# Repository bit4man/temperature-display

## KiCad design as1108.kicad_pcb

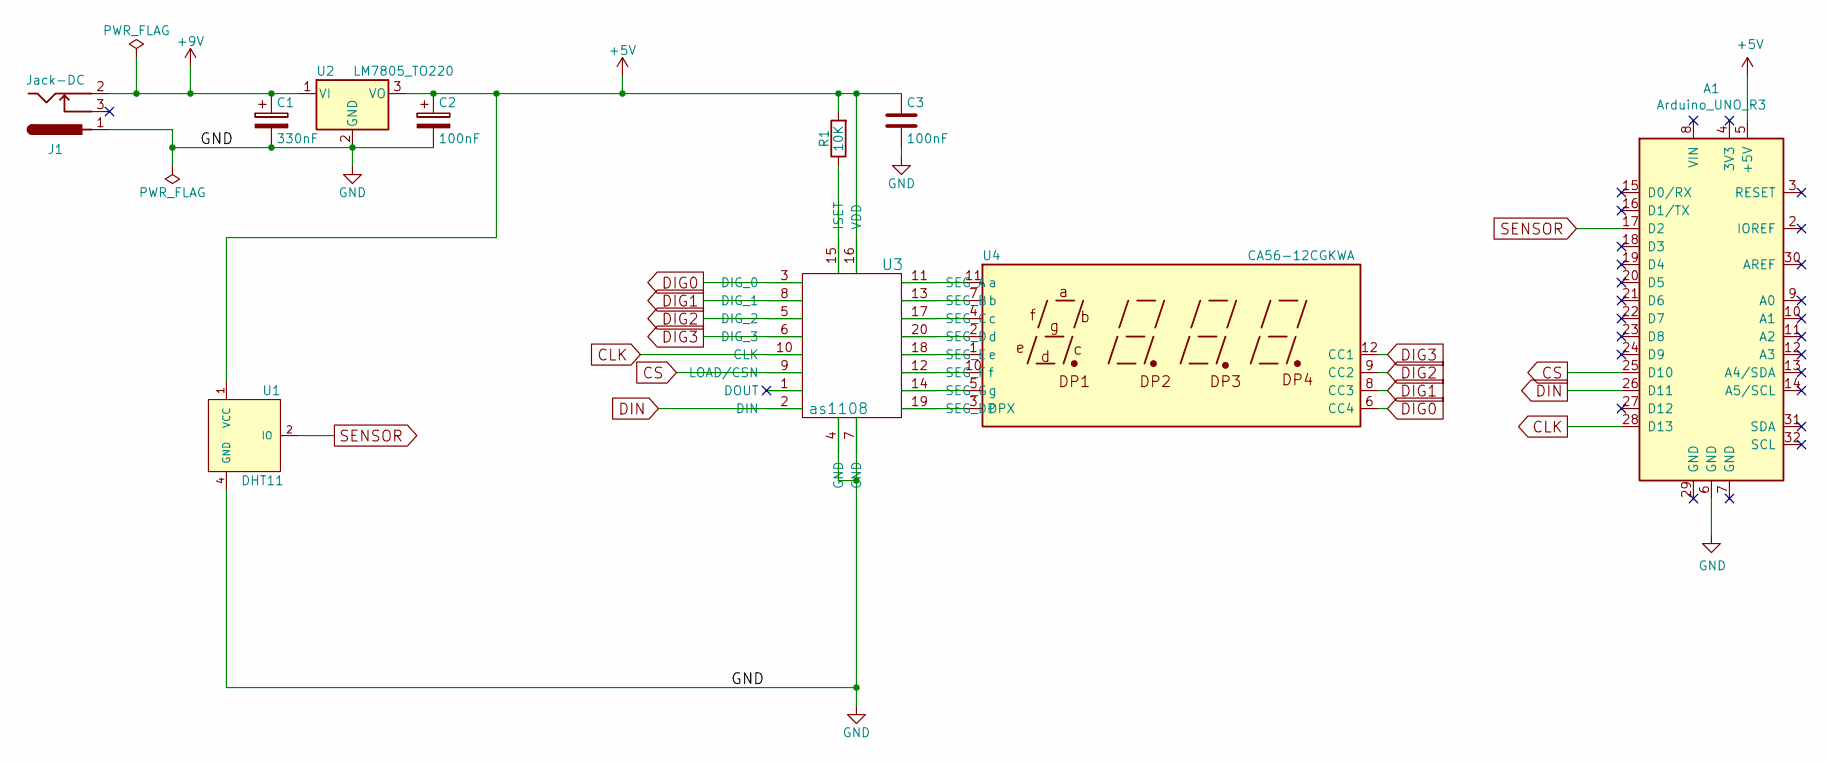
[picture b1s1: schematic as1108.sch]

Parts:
A1: Arduino_UNO_R3; Arduino_Nano_WithMountingHoles
C1: 330nF; CP_Radial_D5.0mm_P2.50mm
C2, C3: 100nF; CP_Radial_D5.0mm_P2.50mm
J1: Jack-DC; BARREL_JACK
R1: 10K; R_Axial_DIN0411_L9.9mm_D3.6mm_P15.24mm_Horizontal
U1: DHT11; Socket_Strip_Straight_1x04_Pitch2.00mm
U2: LM7805_TO220; TO-220_Vertical
U3: as1108; DIP-20_W7.62mm_Socket
U4: CA56-12CGKWA; Cx56-12

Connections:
+5V: A1.5 (+5V), C2.1, C3.1, R1.2, U1.1 (VCC), U2.3 (VO), U3.16 (VDD)
+9V: C1.1, J1.2, U2.1 (VI)
CLK: A1.28 (D13), U3.10 (CLK)
CS: A1.25 (D10), U3.9 (LOAD/CSN)
DIG0: U3.3 (DIG_0), U4.6 (CC4)
DIG1: U3.8 (DIG_1), U4.8 (CC3)
DIG2: U3.5 (DIG_2), U4.9 (CC2)
DIG3: U3.6 (DIG_3), U4.12 (CC1)
DIN: A1.26 (D11), U3.2 (DIN)
GND: A1.6 (GND), C1.2, C2.2, C3.2, J1.1, U1.4 (GND), U2.2 (GND), U3.4 (GND), U3.7 (GND)
unnamed: R1.1, U3.15 (ISET)
unnamed: U3.11 (SEG_A), U4.11 (a)
unnamed: U3.12 (SEG_F), U4.10 (f)
unnamed: U3.13 (SEG_B), U4.7 (b)
unnamed: U3.14 (SEG_G), U4.5 (g)
unnamed: U3.17 (SEG_C), U4.4 (c)
unnamed: U3.18 (SEG_E), U4.1 (e)
unnamed: U3.19 (SEG_DP), U4.3 (DPX)
unnamed: U3.20 (SEG_D), U4.2 (d)
SENSOR: A1.17 (D2), U1.2 (IO)

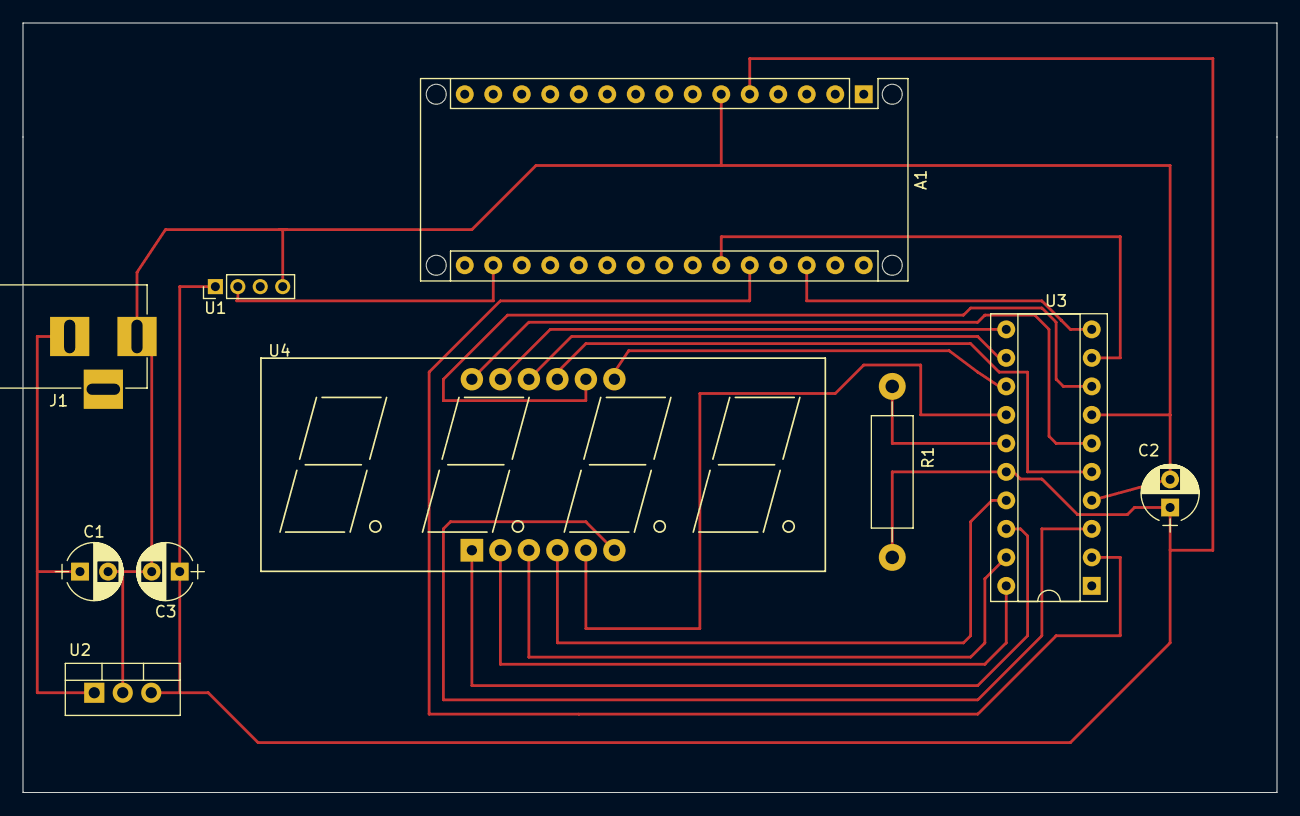
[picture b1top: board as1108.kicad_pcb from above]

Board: 2 copper layers, 111.8 x 68.6 mm, 10 parts (0 on the bottom side), 20 nets.

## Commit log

2018-11-24 Initial
